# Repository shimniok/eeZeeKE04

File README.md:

# eeZeeKE04
Breakout board for Kinetis KE04Z8VTG4

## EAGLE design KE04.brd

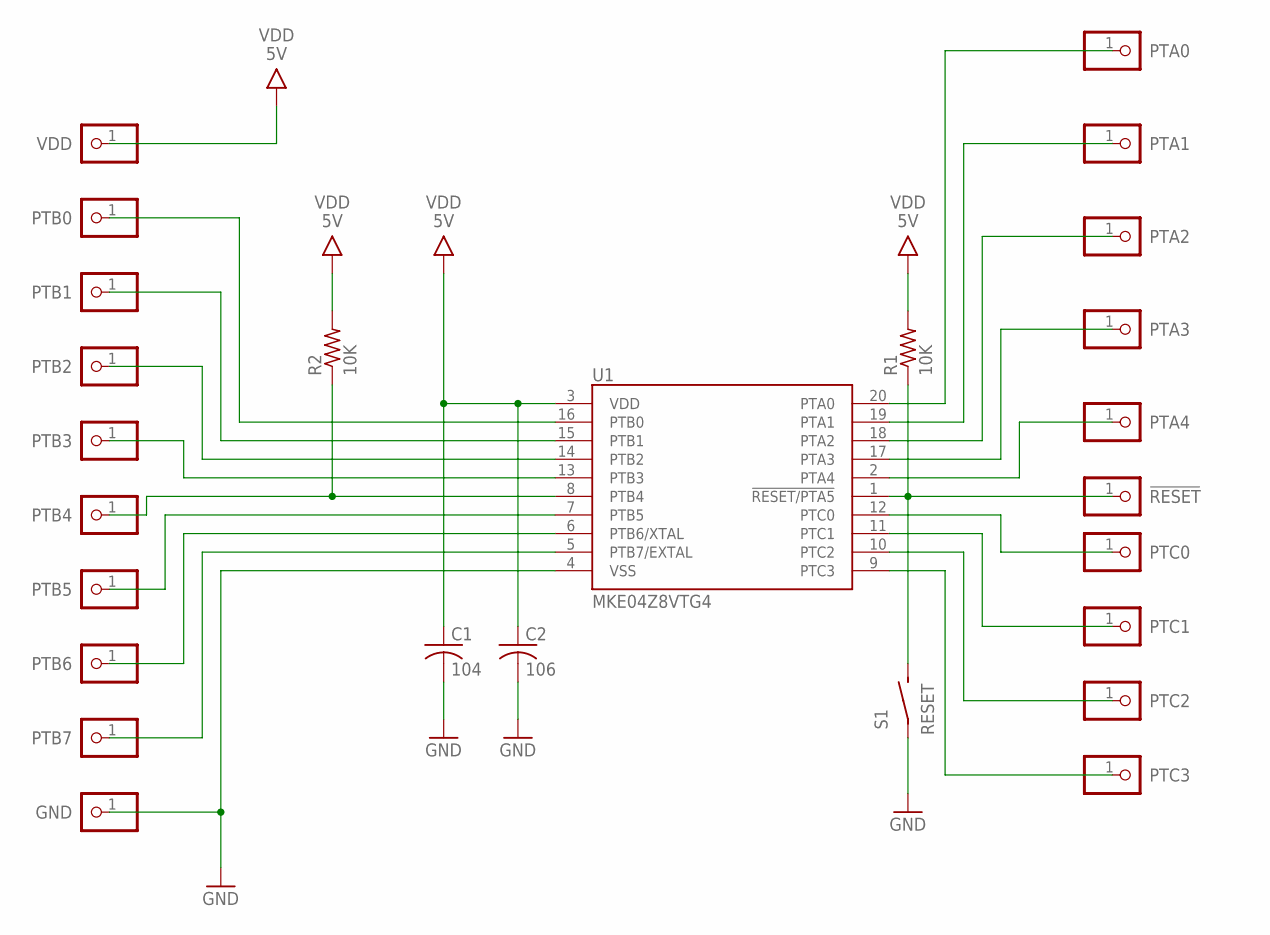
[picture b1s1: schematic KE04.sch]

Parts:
C1: 104; 0603
C2: 106; 1206
JP1: !RESET; 1X01-S
JP2: PTA4; 1X01-S
JP3: VDD; 1X01-S
JP4: GND; 1X01-S
JP5: PTB7; 1X01-S
JP6: PTB6; 1X01-S
JP7: PTB5; 1X01-S
JP8: PTB4; 1X01-S
JP9: PTC3; 1X01-S
JP10: PTC2; 1X01-S
JP11: PTC1; 1X01-S
JP12: PTC0; 1X01-S
JP13: PTB3; 1X01-S
JP14: PTB2; 1X01-S
JP15: PTB1; 1X01-S
JP16: PTB0; 1X01-S
JP17: PTA3; 1X01-S
JP18: PTA2; 1X01-S
JP19: PTA1; 1X01-S
JP20: PTA0; 1X01-S
R1, R2: 10K; 0603
S1: RESET; 3X4X2TACT
U1: MKE04Z8VTG4; TSSOP20

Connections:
GND: C1.2 (-), C2.2 (-), JP4.1, S1.P$1, U1.4 (VSS)
unnamed: JP5.1, U1.5 (PTB7/EXTAL)
unnamed: JP6.1, U1.6 (PTB6/XTAL)
unnamed: JP7.1, U1.7 (PTB5)
unnamed: JP8.1, R2.1, U1.8 (PTB4)
unnamed: JP9.1, U1.9 (PTC3)
unnamed: JP10.1, U1.10 (PTC2)
unnamed: JP11.1, U1.11 (PTC1)
unnamed: JP12.1, U1.12 (PTC0)
unnamed: JP13.1, U1.13 (PTB3)
unnamed: JP14.1, U1.14 (PTB2)
unnamed: JP15.1, U1.15 (PTB1)
unnamed: JP16.1, U1.16 (PTB0)
unnamed: JP17.1, U1.17 (PTA3)
unnamed: JP18.1, U1.18 (PTA2)
unnamed: JP19.1, U1.19 (PTA1)
PTA0: JP20.1, U1.20 (PTA0)
PTA4: JP2.1, U1.2 (PTA4)
PTA5: JP1.1, R1.1, S1.P$2 (S), U1.1 (!RESET/PTA5)
VDD: C1.1 (+), C2.1 (+), JP3.1, R1.2, R2.2, U1.3 (VDD)

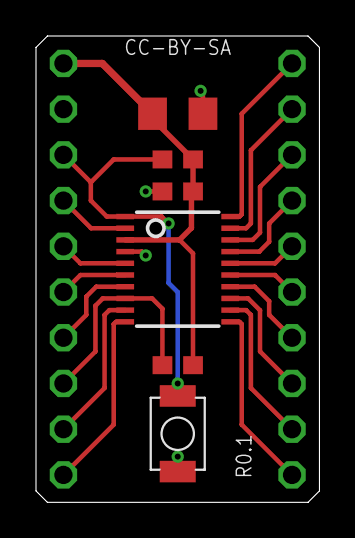
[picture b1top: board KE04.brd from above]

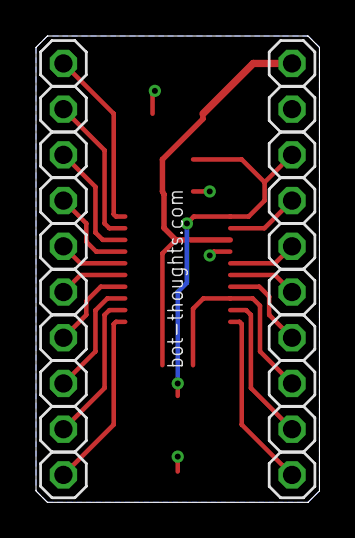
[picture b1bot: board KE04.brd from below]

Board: 2 copper layers, 15.7 x 25.9 mm, 26 parts (20 on the bottom side), 20 nets.

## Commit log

2017-03-17 initial version
2017-03-17 removed extraneous trace

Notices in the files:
KE04.brd:
CC-BY-SA
